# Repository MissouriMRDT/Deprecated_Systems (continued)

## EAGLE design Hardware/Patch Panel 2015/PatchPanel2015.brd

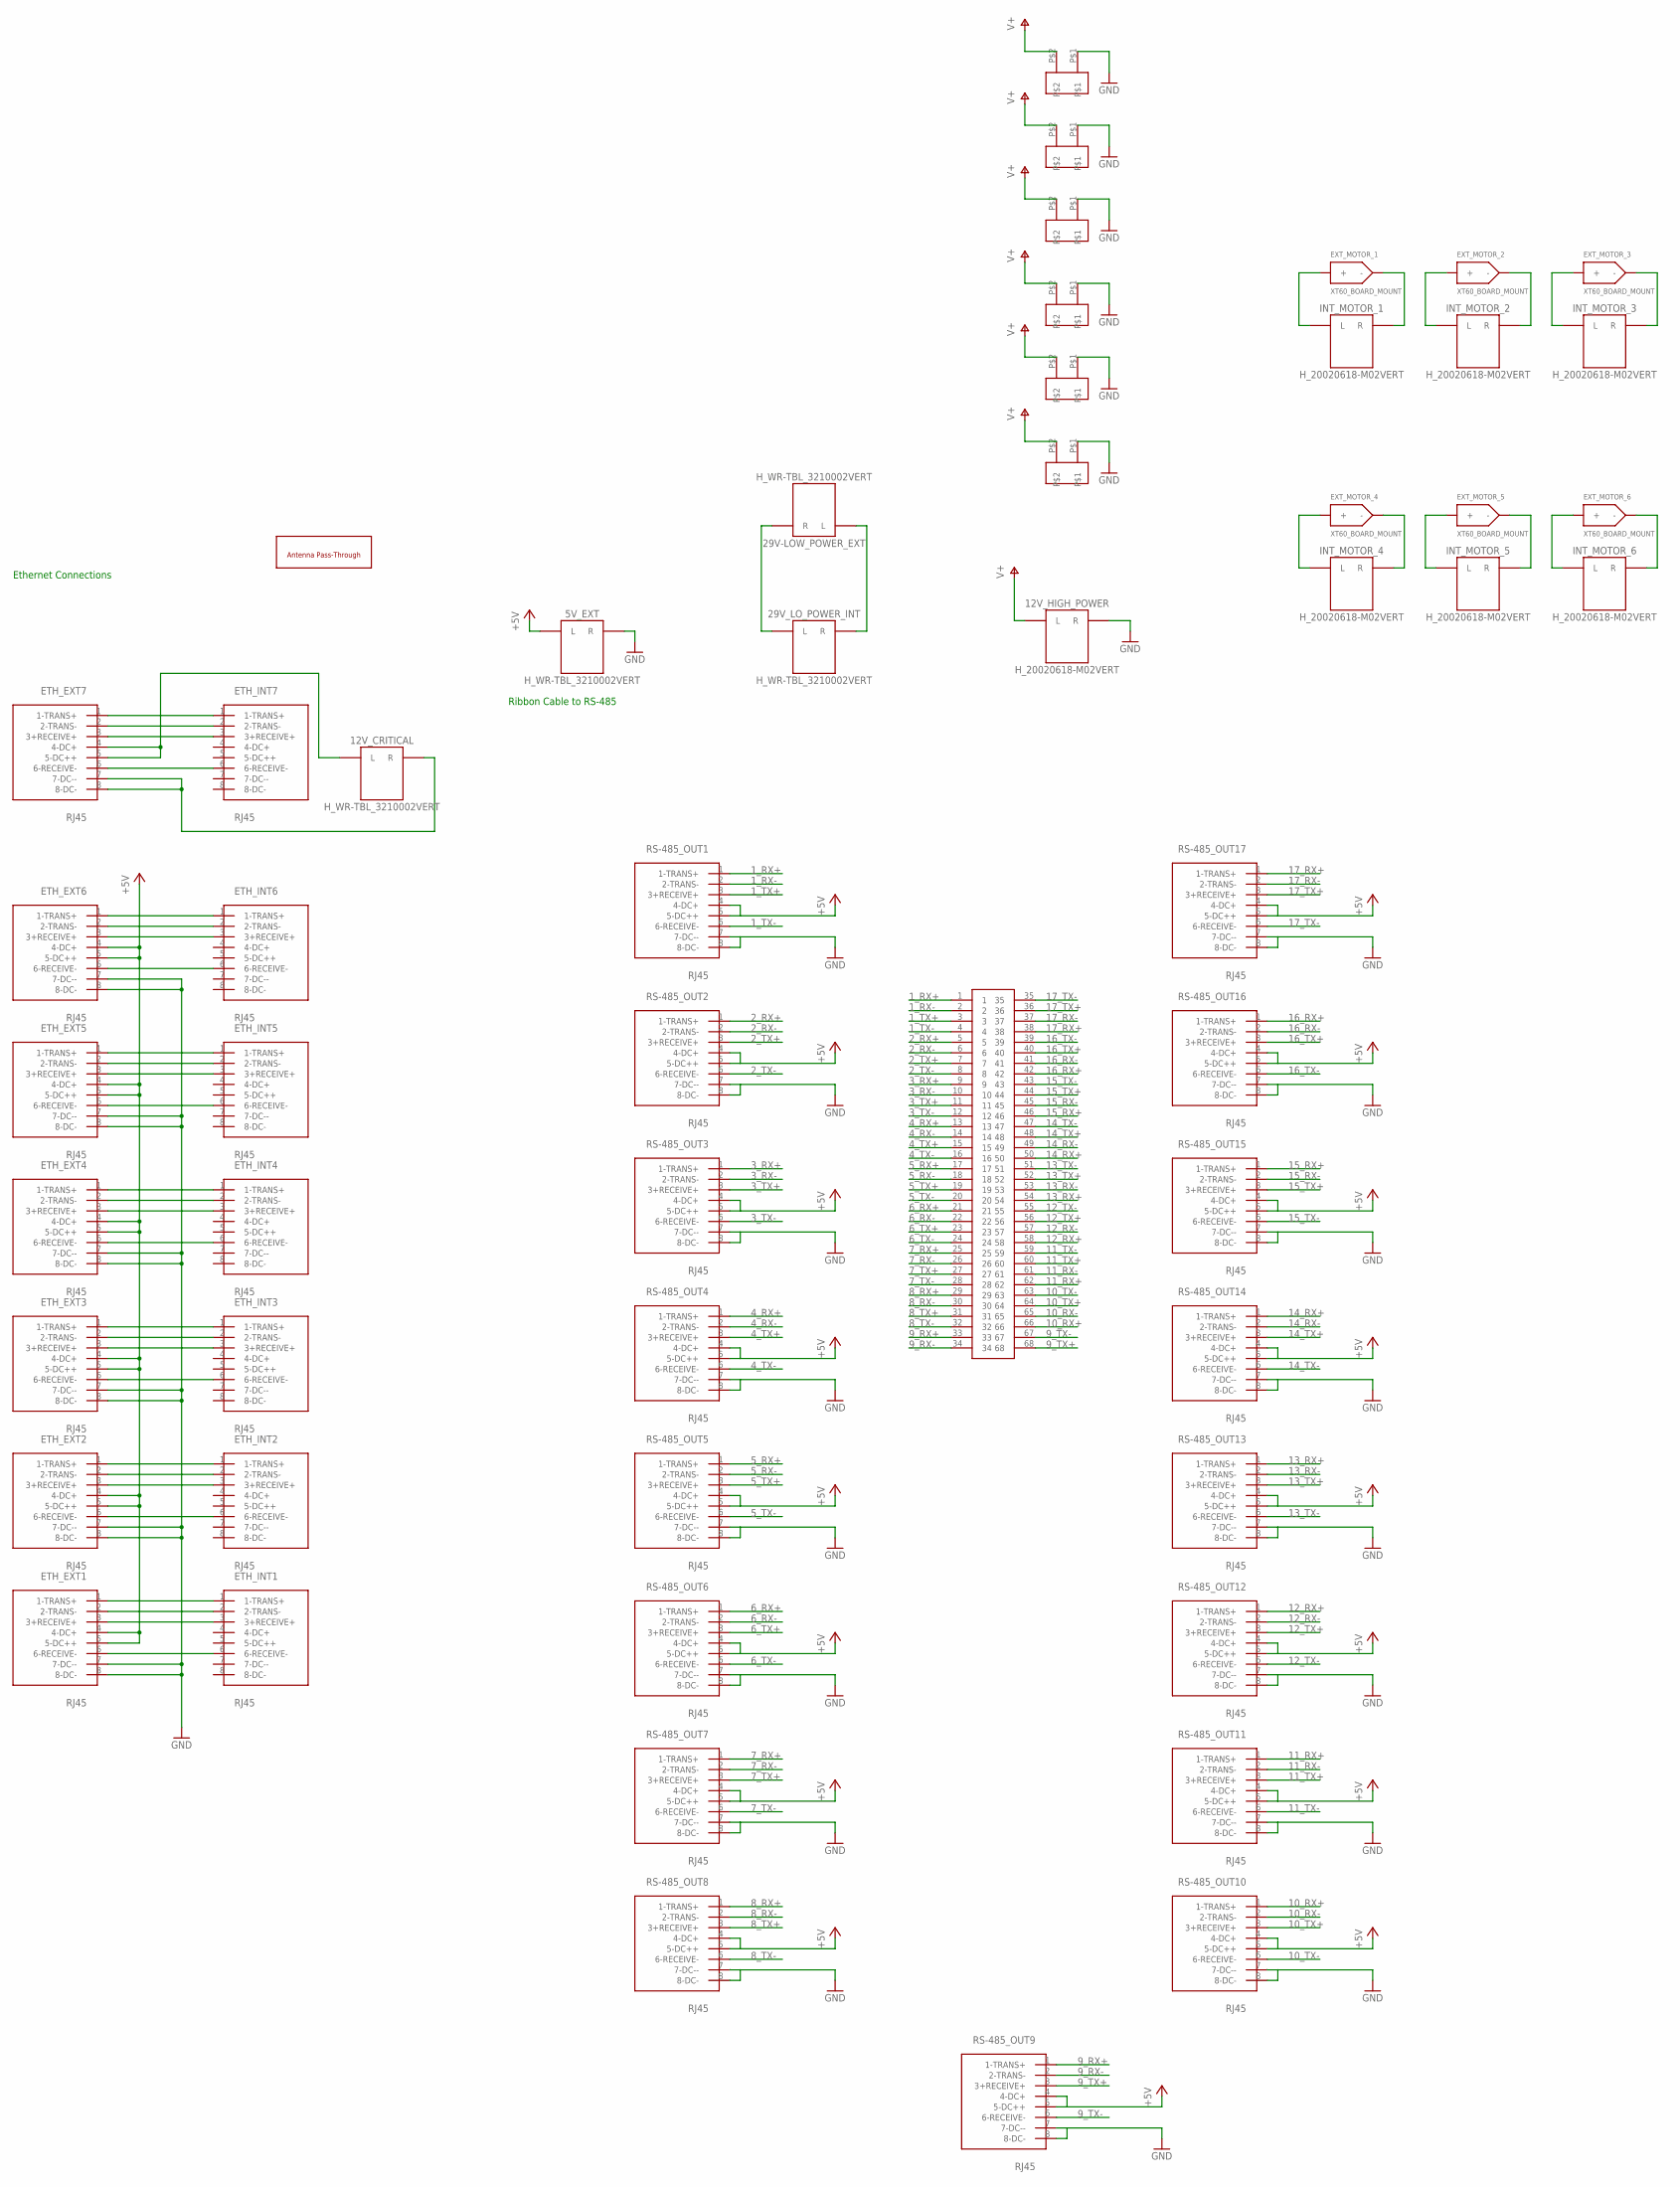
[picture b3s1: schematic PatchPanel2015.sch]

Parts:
5V_EXT, 12V_CRITICAL, 29V-LOW_POWER_EXT, 29V_LO_POWER_INT: H_WR-TBL_3210002VERT; 691321100002
12V_HIGH_POWER: H_20020618-M02VERT; 20020620-M02
ETH_EXT1, ETH_EXT2, ETH_EXT3, ETH_EXT4, ETH_EXT5, ETH_EXT6, ETH_EXT7: RJ45; RJ45-CAT5E
ETH_INT1, ETH_INT2, ETH_INT3, ETH_INT4, ETH_INT5, ETH_INT6, ETH_INT7: RJ45; RJ45-CAT5E
EXT_MOTOR_1, EXT_MOTOR_2, EXT_MOTOR_3, EXT_MOTOR_4, EXT_MOTOR_5, EXT_MOTOR_6: XT60_BOARD_MOUNT; XT60_BOARD
INT_MOTOR_1, INT_MOTOR_2, INT_MOTOR_3, INT_MOTOR_4, INT_MOTOR_5, INT_MOTOR_6: H_20020618-M02VERT; 20020620-M02
RS-485_OUT1, RS-485_OUT2, RS-485_OUT3, RS-485_OUT4, RS-485_OUT5, RS-485_OUT6, RS-485_OUT7, RS-485_OUT8, RS-485_OUT9, RS-485_OUT10, RS-485_OUT11, RS-485_OUT12, RS-485_OUT13, RS-485_OUT14, RS-485_OUT15, RS-485_OUT16, RS-485_OUT17: RJ45; RJ45-CAT5E
U$1, U$2, U$3, U$5, U$6, U$8: MLX-2; 42002-2
U$4: TB60050685100; 60050685100
U$16: SMA-THRU; SMA

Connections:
1_RX+: RS-485_OUT1.1 (1-TRANS+), U$4.1
1_RX-: RS-485_OUT1.2 (2-TRANS-), U$4.2
1_TX+: RS-485_OUT1.3 (3+RECEIVE+), U$4.3
1_TX-: RS-485_OUT1.6 (6-RECEIVE-), U$4.4
2_RX+: RS-485_OUT2.1 (1-TRANS+), U$4.5
2_RX-: RS-485_OUT2.2 (2-TRANS-), U$4.6
2_TX+: RS-485_OUT2.3 (3+RECEIVE+), U$4.7
2_TX-: RS-485_OUT2.6 (6-RECEIVE-), U$4.8
3_RX+: RS-485_OUT3.1 (1-TRANS+), U$4.9
3_RX-: RS-485_OUT3.2 (2-TRANS-), U$4.10
3_TX+: RS-485_OUT3.3 (3+RECEIVE+), U$4.11
3_TX-: RS-485_OUT3.6 (6-RECEIVE-), U$4.12
4_RX+: RS-485_OUT4.1 (1-TRANS+), U$4.13
4_RX-: RS-485_OUT4.2 (2-TRANS-), U$4.14
4_TX+: RS-485_OUT4.3 (3+RECEIVE+), U$4.15
4_TX-: RS-485_OUT4.6 (6-RECEIVE-), U$4.16
5_RX+: RS-485_OUT5.1 (1-TRANS+), U$4.17
5_RX-: RS-485_OUT5.2 (2-TRANS-), U$4.18
5_TX+: RS-485_OUT5.3 (3+RECEIVE+), U$4.19
5_TX-: RS-485_OUT5.6 (6-RECEIVE-), U$4.20
6_RX+: RS-485_OUT6.1 (1-TRANS+), U$4.21
6_RX-: RS-485_OUT6.2 (2-TRANS-), U$4.22
6_TX+: RS-485_OUT6.3 (3+RECEIVE+), U$4.23
6_TX-: RS-485_OUT6.6 (6-RECEIVE-), U$4.24
7_RX+: RS-485_OUT7.1 (1-TRANS+), U$4.25
7_RX-: RS-485_OUT7.2 (2-TRANS-), U$4.26
7_TX+: RS-485_OUT7.3 (3+RECEIVE+), U$4.27
7_TX-: RS-485_OUT7.6 (6-RECEIVE-), U$4.28
8_RX+: RS-485_OUT8.1 (1-TRANS+), U$4.29
8_RX-: RS-485_OUT8.2 (2-TRANS-), U$4.30
8_TX+: RS-485_OUT8.3 (3+RECEIVE+), U$4.31
8_TX-: RS-485_OUT8.6 (6-RECEIVE-), U$4.32
9_RX+: RS-485_OUT9.1 (1-TRANS+), U$4.33
9_RX-: RS-485_OUT9.2 (2-TRANS-), U$4.34
9_TX+: RS-485_OUT9.3 (3+RECEIVE+), U$4.68
9_TX-: RS-485_OUT9.6 (6-RECEIVE-), U$4.67
10_RX+: RS-485_OUT10.1 (1-TRANS+), U$4.66
10_RX-: RS-485_OUT10.2 (2-TRANS-), U$4.65
10_TX+: RS-485_OUT10.3 (3+RECEIVE+), U$4.64
10_TX-: RS-485_OUT10.6 (6-RECEIVE-), U$4.63
11_RX+: RS-485_OUT11.1 (1-TRANS+), U$4.62
11_RX-: RS-485_OUT11.2 (2-TRANS-), U$4.61
11_TX+: RS-485_OUT11.3 (3+RECEIVE+), U$4.60
11_TX-: RS-485_OUT11.6 (6-RECEIVE-), U$4.59
12_RX+: RS-485_OUT12.1 (1-TRANS+), U$4.58
12_RX-: RS-485_OUT12.2 (2-TRANS-), U$4.57
12_TX+: RS-485_OUT12.3 (3+RECEIVE+), U$4.56
12_TX-: RS-485_OUT12.6 (6-RECEIVE-), U$4.55
13_RX+: RS-485_OUT13.1 (1-TRANS+), U$4.54
13_RX-: RS-485_OUT13.2 (2-TRANS-), U$4.53
13_TX+: RS-485_OUT13.3 (3+RECEIVE+), U$4.52
13_TX-: RS-485_OUT13.6 (6-RECEIVE-), U$4.51
14_RX+: RS-485_OUT14.1 (1-TRANS+), U$4.50
14_RX-: RS-485_OUT14.2 (2-TRANS-), U$4.49
14_TX+: RS-485_OUT14.3 (3+RECEIVE+), U$4.48
14_TX-: RS-485_OUT14.6 (6-RECEIVE-), U$4.47
15_RX+: RS-485_OUT15.1 (1-TRANS+), U$4.46
15_RX-: RS-485_OUT15.2 (2-TRANS-), U$4.45
15_TX+: RS-485_OUT15.3 (3+RECEIVE+), U$4.44
15_TX-: RS-485_OUT15.6 (6-RECEIVE-), U$4.43
16_RX+: RS-485_OUT16.1 (1-TRANS+), U$4.42
16_RX-: RS-485_OUT16.2 (2-TRANS-), U$4.41
16_TX+: RS-485_OUT16.3 (3+RECEIVE+), U$4.40
16_TX-: RS-485_OUT16.6 (6-RECEIVE-), U$4.39
17_RX+: RS-485_OUT17.1 (1-TRANS+), U$4.38
17_RX-: RS-485_OUT17.2 (2-TRANS-), U$4.37
17_TX+: RS-485_OUT17.3 (3+RECEIVE+), U$4.36
17_TX-: RS-485_OUT17.6 (6-RECEIVE-), U$4.35
+5V: 5V_EXT.L, ETH_EXT1.4 (4-DC+), ETH_EXT1.5 (5-DC++), ETH_EXT2.4 (4-DC+), ETH_EXT2.5 (5-DC++), ETH_EXT3.4 (4-DC+), ETH_EXT3.5 (5-DC++), ETH_EXT4.4 (4-DC+), ETH_EXT4.5 (5-DC++), ETH_EXT5.4 (4-DC+), ETH_EXT5.5 (5-DC++), ETH_EXT6.4 (4-DC+), ETH_EXT6.5 (5-DC++), RS-485_OUT1.4 (4-DC+), RS-485_OUT1.5 (5-DC++), RS-485_OUT2.4 (4-DC+), RS-485_OUT2.5 (5-DC++), RS-485_OUT3.4 (4-DC+), RS-485_OUT3.5 (5-DC++), RS-485_OUT4.4 (4-DC+), RS-485_OUT4.5 (5-DC++), RS-485_OUT5.4 (4-DC+), RS-485_OUT5.5 (5-DC++), RS-485_OUT6.4 (4-DC+), RS-485_OUT6.5 (5-DC++), RS-485_OUT7.4 (4-DC+), RS-485_OUT7.5 (5-DC++), RS-485_OUT8.4 (4-DC+), RS-485_OUT8.5 (5-DC++), RS-485_OUT9.4 (4-DC+), RS-485_OUT9.5 (5-DC++), RS-485_OUT10.4 (4-DC+), RS-485_OUT10.5 (5-DC++), RS-485_OUT11.4 (4-DC+), RS-485_OUT11.5 (5-DC++), RS-485_OUT12.4 (4-DC+), RS-485_OUT12.5 (5-DC++), RS-485_OUT13.4 (4-DC+), RS-485_OUT13.5 (5-DC++), RS-485_OUT14.4 (4-DC+), RS-485_OUT14.5 (5-DC++), RS-485_OUT15.4 (4-DC+), RS-485_OUT15.5 (5-DC++), RS-485_OUT16.4 (4-DC+), RS-485_OUT16.5 (5-DC++), RS-485_OUT17.4 (4-DC+), RS-485_OUT17.5 (5-DC++)
GND: 5V_EXT.R, 12V_HIGH_POWER.R1 (R), 12V_HIGH_POWER.R2 (R), ETH_EXT1.7 (7-DC--), ETH_EXT1.8 (8-DC-), ETH_EXT2.7 (7-DC--), ETH_EXT2.8 (8-DC-), ETH_EXT3.7 (7-DC--), ETH_EXT3.8 (8-DC-), ETH_EXT4.7 (7-DC--), ETH_EXT4.8 (8-DC-), ETH_EXT5.7 (7-DC--), ETH_EXT5.8 (8-DC-), ETH_EXT6.7 (7-DC--), ETH_EXT6.8 (8-DC-), RS-485_OUT1.7 (7-DC--), RS-485_OUT1.8 (8-DC-), RS-485_OUT2.7 (7-DC--), RS-485_OUT2.8 (8-DC-), RS-485_OUT3.7 (7-DC--), RS-485_OUT3.8 (8-DC-), RS-485_OUT4.7 (7-DC--), RS-485_OUT4.8 (8-DC-), RS-485_OUT5.7 (7-DC--), RS-485_OUT5.8 (8-DC-), RS-485_OUT6.7 (7-DC--), RS-485_OUT6.8 (8-DC-), RS-485_OUT7.7 (7-DC--), RS-485_OUT7.8 (8-DC-), RS-485_OUT8.7 (7-DC--), RS-485_OUT8.8 (8-DC-), RS-485_OUT9.7 (7-DC--), RS-485_OUT9.8 (8-DC-), RS-485_OUT10.7 (7-DC--), RS-485_OUT10.8 (8-DC-), RS-485_OUT11.7 (7-DC--), RS-485_OUT11.8 (8-DC-), RS-485_OUT12.7 (7-DC--), RS-485_OUT12.8 (8-DC-), RS-485_OUT13.7 (7-DC--), RS-485_OUT13.8 (8-DC-), RS-485_OUT14.7 (7-DC--), RS-485_OUT14.8 (8-DC-), RS-485_OUT15.7 (7-DC--), RS-485_OUT15.8 (8-DC-), RS-485_OUT16.7 (7-DC--), RS-485_OUT16.8 (8-DC-), RS-485_OUT17.7 (7-DC--), RS-485_OUT17.8 (8-DC-), U$1.P$1, U$2.P$1, U$3.P$1, U$5.P$1, U$6.P$1, U$8.P$1
unnamed: ETH_EXT1.1 (1-TRANS+), ETH_INT1.1 (1-TRANS+)
unnamed: ETH_EXT1.2 (2-TRANS-), ETH_INT1.2 (2-TRANS-)
unnamed: ETH_EXT1.3 (3+RECEIVE+), ETH_INT1.3 (3+RECEIVE+)
unnamed: EXT_MOTOR_1.POS (+), INT_MOTOR_1.L1 (L), INT_MOTOR_1.L2 (L)
unnamed: EXT_MOTOR_1.NEG (-), INT_MOTOR_1.R1 (R), INT_MOTOR_1.R2 (R)
unnamed: ETH_EXT1.6 (6-RECEIVE-), ETH_INT1.6 (6-RECEIVE-)
unnamed: EXT_MOTOR_2.POS (+), INT_MOTOR_2.L1 (L), INT_MOTOR_2.L2 (L)
unnamed: EXT_MOTOR_2.NEG (-), INT_MOTOR_2.R1 (R), INT_MOTOR_2.R2 (R)
unnamed: ETH_EXT2.1 (1-TRANS+), ETH_INT2.1 (1-TRANS+)
unnamed: ETH_EXT2.2 (2-TRANS-), ETH_INT2.2 (2-TRANS-)
unnamed: ETH_EXT2.3 (3+RECEIVE+), ETH_INT2.3 (3+RECEIVE+)
unnamed: EXT_MOTOR_3.POS (+), INT_MOTOR_3.L1 (L), INT_MOTOR_3.L2 (L)
unnamed: EXT_MOTOR_3.NEG (-), INT_MOTOR_3.R1 (R), INT_MOTOR_3.R2 (R)
unnamed: ETH_EXT2.6 (6-RECEIVE-), ETH_INT2.6 (6-RECEIVE-)
unnamed: EXT_MOTOR_4.POS (+), INT_MOTOR_4.L1 (L), INT_MOTOR_4.L2 (L)
unnamed: EXT_MOTOR_4.NEG (-), INT_MOTOR_4.R1 (R), INT_MOTOR_4.R2 (R)
unnamed: ETH_EXT3.1 (1-TRANS+), ETH_INT3.1 (1-TRANS+)
unnamed: ETH_EXT3.2 (2-TRANS-), ETH_INT3.2 (2-TRANS-)
unnamed: ETH_EXT3.3 (3+RECEIVE+), ETH_INT3.3 (3+RECEIVE+)
unnamed: EXT_MOTOR_5.POS (+), INT_MOTOR_5.L1 (L), INT_MOTOR_5.L2 (L)
unnamed: EXT_MOTOR_5.NEG (-), INT_MOTOR_5.R1 (R), INT_MOTOR_5.R2 (R)
unnamed: ETH_EXT3.6 (6-RECEIVE-), ETH_INT3.6 (6-RECEIVE-)
unnamed: EXT_MOTOR_6.POS (+), INT_MOTOR_6.L1 (L), INT_MOTOR_6.L2 (L)
unnamed: EXT_MOTOR_6.NEG (-), INT_MOTOR_6.R1 (R), INT_MOTOR_6.R2 (R)
unnamed: 29V-LOW_POWER_EXT.R, 29V_LO_POWER_INT.L
unnamed: ETH_EXT4.6 (6-RECEIVE-), ETH_INT4.6 (6-RECEIVE-)
unnamed: 29V-LOW_POWER_EXT.L, 29V_LO_POWER_INT.R
unnamed: 12V_CRITICAL.L, ETH_EXT7.4 (4-DC+), ETH_EXT7.5 (5-DC++)
unnamed: ETH_EXT4.3 (3+RECEIVE+), ETH_INT4.3 (3+RECEIVE+)
unnamed: ETH_EXT4.2 (2-TRANS-), ETH_INT4.2 (2-TRANS-)
unnamed: ETH_EXT4.1 (1-TRANS+), ETH_INT4.1 (1-TRANS+)
unnamed: 12V_CRITICAL.R, ETH_EXT7.7 (7-DC--), ETH_EXT7.8 (8-DC-)
unnamed: ETH_EXT5.6 (6-RECEIVE-), ETH_INT5.6 (6-RECEIVE-)
unnamed: ETH_EXT5.3 (3+RECEIVE+), ETH_INT5.3 (3+RECEIVE+)
unnamed: ETH_EXT5.2 (2-TRANS-), ETH_INT5.2 (2-TRANS-)
unnamed: ETH_EXT5.1 (1-TRANS+), ETH_INT5.1 (1-TRANS+)
unnamed: ETH_EXT6.1 (1-TRANS+), ETH_INT6.1 (1-TRANS+)
unnamed: ETH_EXT6.2 (2-TRANS-), ETH_INT6.2 (2-TRANS-)
unnamed: ETH_EXT6.3 (3+RECEIVE+), ETH_INT6.3 (3+RECEIVE+)
unnamed: ETH_EXT6.6 (6-RECEIVE-), ETH_INT6.6 (6-RECEIVE-)
unnamed: ETH_EXT7.1 (1-TRANS+), ETH_INT7.1 (1-TRANS+)
unnamed: ETH_EXT7.2 (2-TRANS-), ETH_INT7.2 (2-TRANS-)
unnamed: ETH_EXT7.3 (3+RECEIVE+), ETH_INT7.3 (3+RECEIVE+)
unnamed: ETH_EXT7.6 (6-RECEIVE-), ETH_INT7.6 (6-RECEIVE-)
V+: 12V_HIGH_POWER.L1 (L), 12V_HIGH_POWER.L2 (L), U$1.P$2, U$2.P$2, U$3.P$2, U$5.P$2, U$6.P$2, U$8.P$2

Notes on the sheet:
Ethernet Connections
Ribbon Cable to RS-485

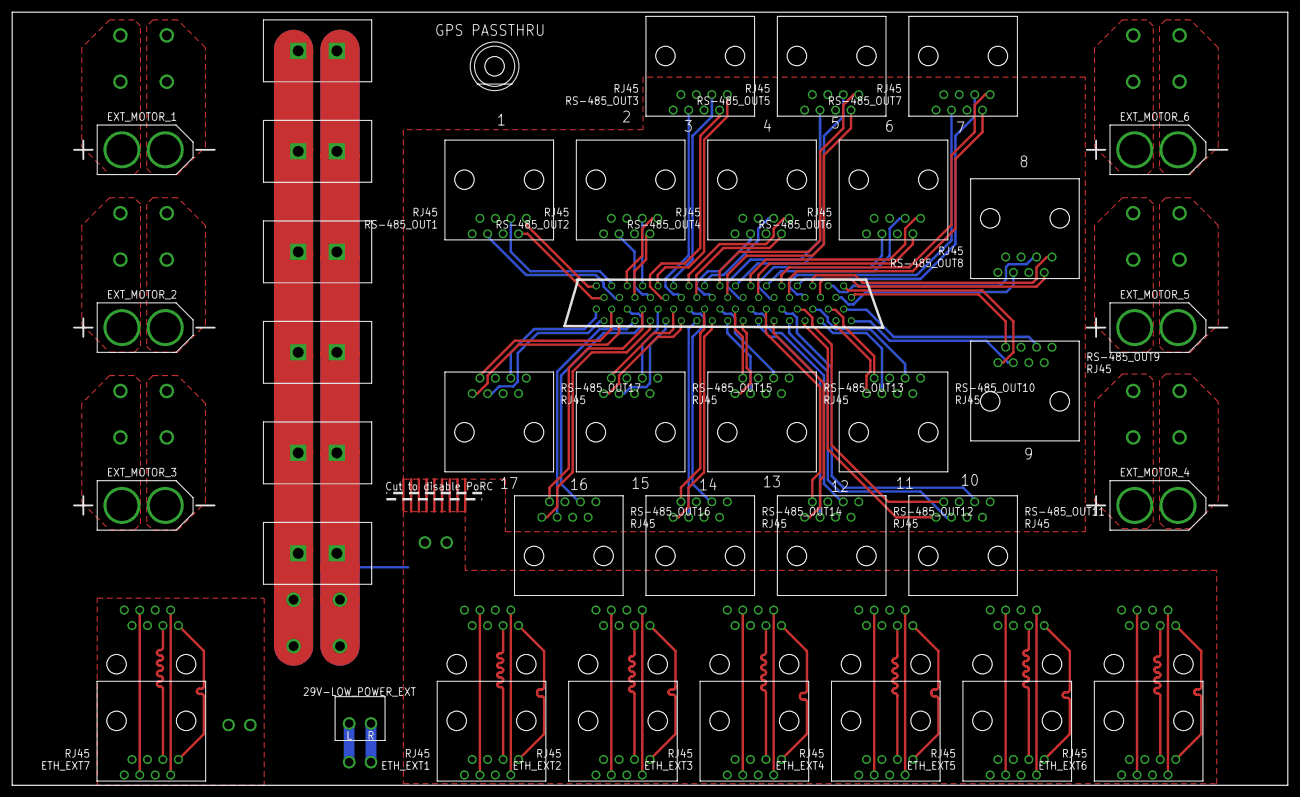
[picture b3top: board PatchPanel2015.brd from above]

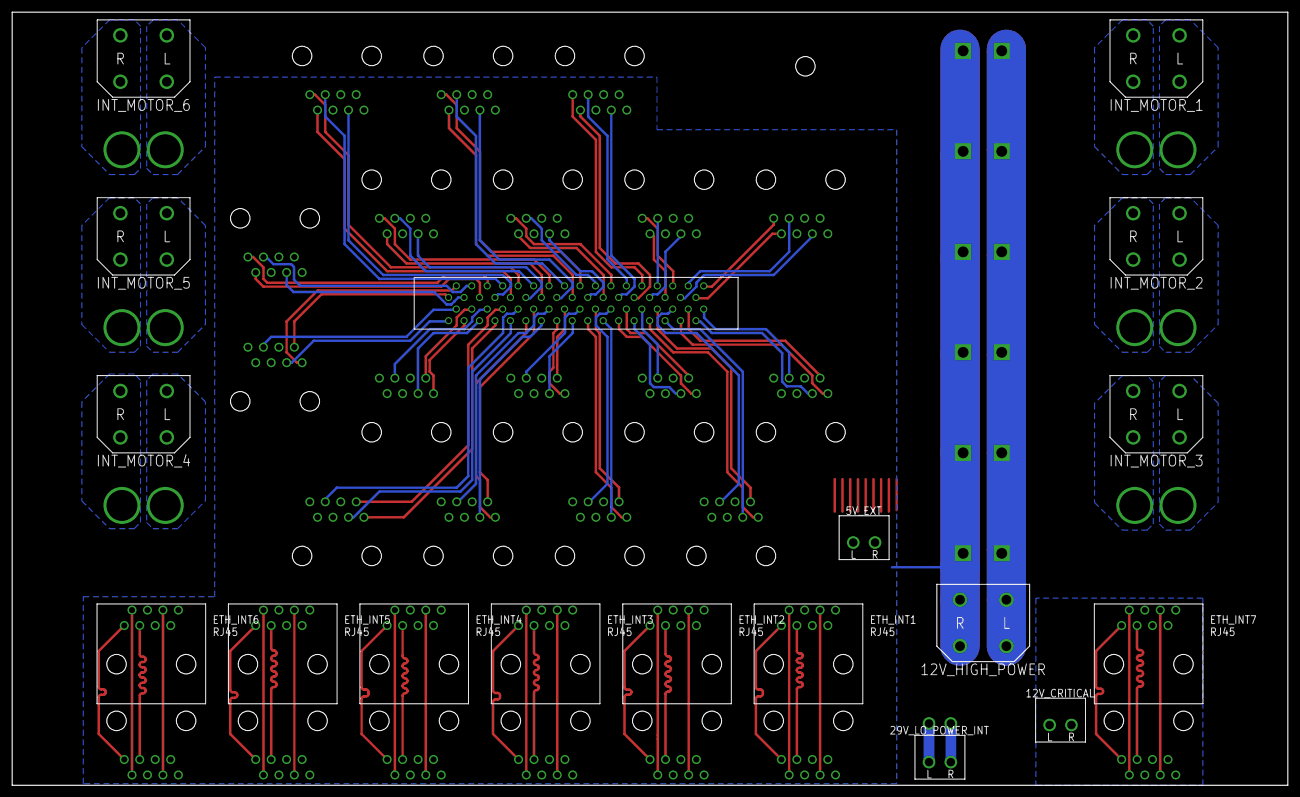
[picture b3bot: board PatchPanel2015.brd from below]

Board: 2 copper layers, 209.6 x 127.0 mm, 56 parts (18 on the bottom side), 115 nets.

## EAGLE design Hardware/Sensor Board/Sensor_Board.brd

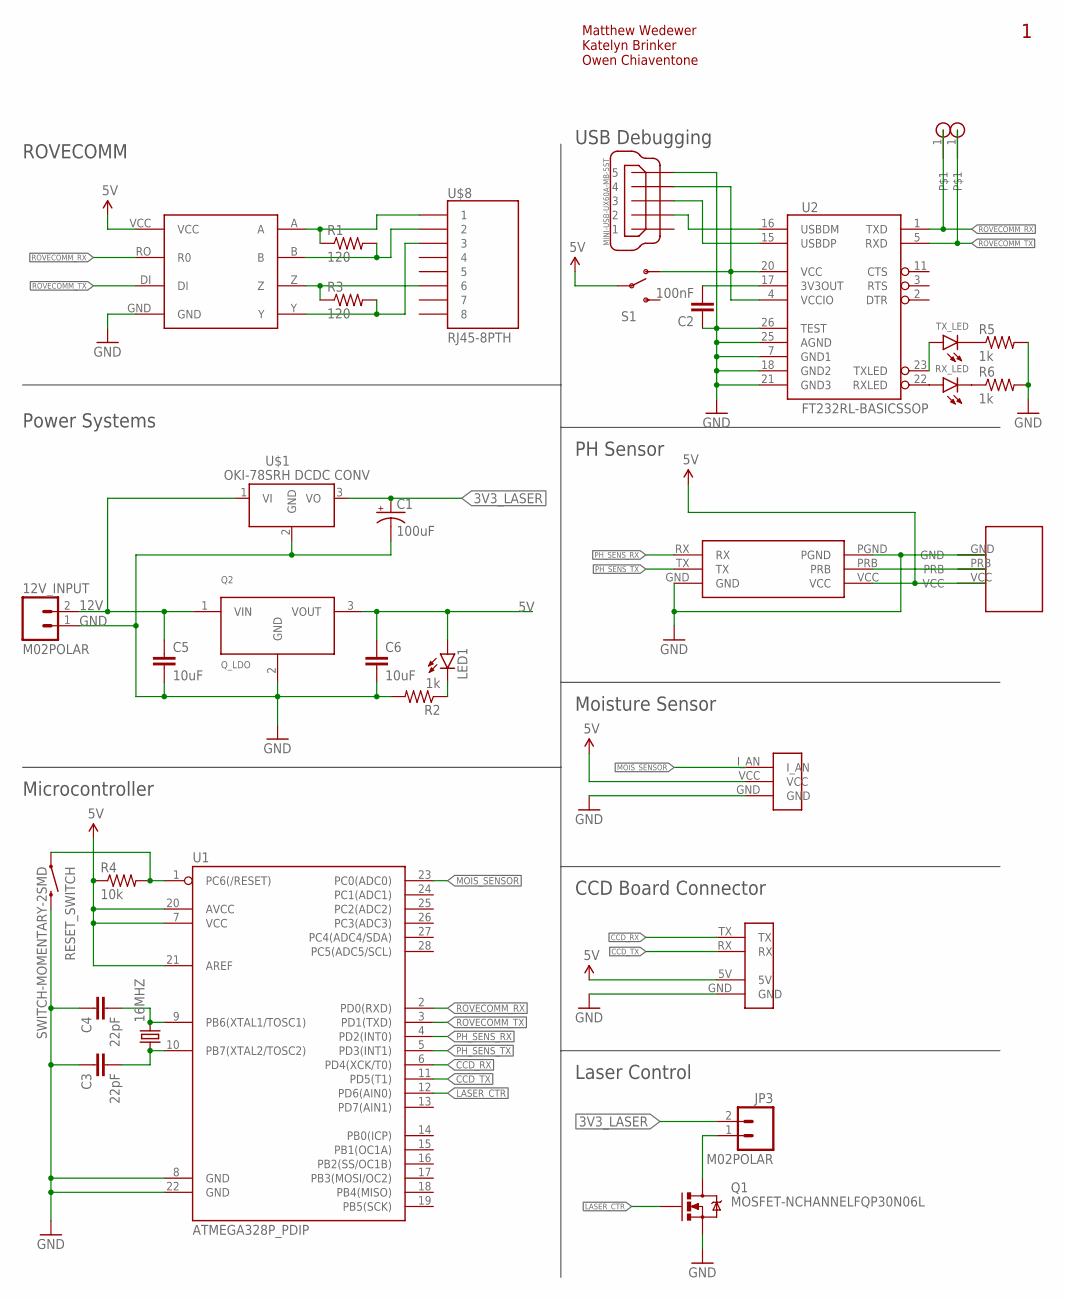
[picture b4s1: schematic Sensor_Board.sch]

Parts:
12V_INPUT: M02POLAR; MOLEX-1X2
16MHZ: CRYSTALHC49US; HC49US
C1: 100uF; CPOL-RADIAL-100UF-25V
C2: 100nF; 1206
C3, C4: 22pF; 1206
C5, C6: 10uF; 1206
DEBUG_RX: J_HOLE; J_AWG20
DEBUG_TX: J_HOLE; J_AWG20
JP3: M02POLAR; MOLEX-1X2
LED1: LED1206; LED-1206
Q1: MOSFET-NCHANNELFQP30N06L; TO220V
Q2: Q_LDO; TO-220
R1, R3: 120; 1206
R2, R5, R6: 1k; 1206
R4: 10k; 1206
RESET_SWITCH: SWITCH-MOMENTARY-2SMD; TACTILE-SWITCH-SMD
RX_LED: LED1206; LED-1206
S1: SWITCH-SPDTPTH; SWITCH-SPDT
TX_LED: LED1206; LED-1206
U1: ATMEGA328P_PDIP; DIL28-3
U2: FT232RL-BASICSSOP; SSOP28DB
U$1: Q_OKI-78SR; OKI-78SRH
U$3: PH_EZ0
U$4: PH_CONNECTOR
U$5: MOISTURE_SENSOR
U$6: CCD_CONNECTOR
U$7: MAX3077; MAX3070E
U$8: RJ45-8PTH; RJ45-8
X1: MINI-USB-UX60A-MB-5ST; UX60A-MB-5ST

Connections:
3V3_LASER: C1.1 (+), JP3.2, U$1.3 (VO)
5V: C6.1, LED1.A, Q2.3 (VOUT), R4.1, S1.2, U1.7 (VCC), U1.20 (AVCC), U1.21 (AREF), U$3.VCC, U$4.VCC, U$5.VCC, U$6.5V, U$7.VCC
5V1: TX_LED.A, U2.23 (TXLED)
12V: 12V_INPUT.2, C5.1, Q2.1 (VIN), U$1.1 (VI)
CCD_RX: U1.6 (PD4(XCK/T0)), U$6.TX
CCD_TX: U1.11 (PD5(T1)), U$6.RX
GND: 12V_INPUT.1, C1.2 (-), C2.1, C3.1, C4.1, C5.2, C6.2, Q1.3 (S), Q2.2 (GND), R2.2, R5.2, R6.2, RESET_SWITCH.3 (2), U1.8 (GND), U1.22 (GND), U2.7 (GND1), U2.18 (GND2), U2.21 (GND3), U2.25 (AGND), U2.26 (TEST), U$1.2 (GND), U$3.GND, U$3.PGND, U$4.GND, U$5.GND, U$6.GND, U$7.GND, X1.5
LASER_CTR: Q1.1 (G), U1.12 (PD6(AIN0))
MOIS_SENSOR: U1.23 (PC0(ADC0)), U$5.I_AN
unnamed: JP3.1, Q1.2 (D)
unnamed: 16MHZ.2, C4.2, U1.9 (PB6(XTAL1/TOSC1))
unnamed: LED1.C, R2.1
unnamed: 16MHZ.1, C3.2, U1.10 (PB7(XTAL2/TOSC2))
unnamed: U$3.PRB, U$4.PRB
unnamed: R1.1, U$7.A, U$8.1
unnamed: R1.2, U$7.B, U$8.2
unnamed: R3.1, U$7.Z, U$8.6
unnamed: R3.2, U$7.Y, U$8.3
unnamed: R4.2, RESET_SWITCH.1, U1.1 (PC6(/RESET))
unnamed: C2.2, U2.17 (3V3OUT)
unnamed: U2.16 (USBDM), X1.2
unnamed: U2.15 (USBDP), X1.3
unnamed: S1.1 (O), U2.4 (VCCIO), U2.20 (VCC), X1.4
unnamed: R5.1, TX_LED.C
unnamed: RX_LED.A, U2.22 (RXLED)
unnamed: R6.1, RX_LED.C
PH_SENS_RX: U1.4 (PD2(INT0)), U$3.RX
PH_SENS_TX: U1.5 (PD3(INT1)), U$3.TX
ROVECOMM_RX: DEBUG_RX.1, U1.2 (PD0(RXD)), U2.1 (TXD), U$7.RO (R0)
ROVECOMM_TX: DEBUG_TX.1, U1.3 (PD1(TXD)), U2.5 (RXD), U$7.DI

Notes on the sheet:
Laser Control
CCD Board Connector
PH Sensor
Moisture Sensor
Power Systems
Microcontroller
ROVECOMM
USB Debugging
Matthew Wedewer Katelyn Brinker Owen Chiaventone

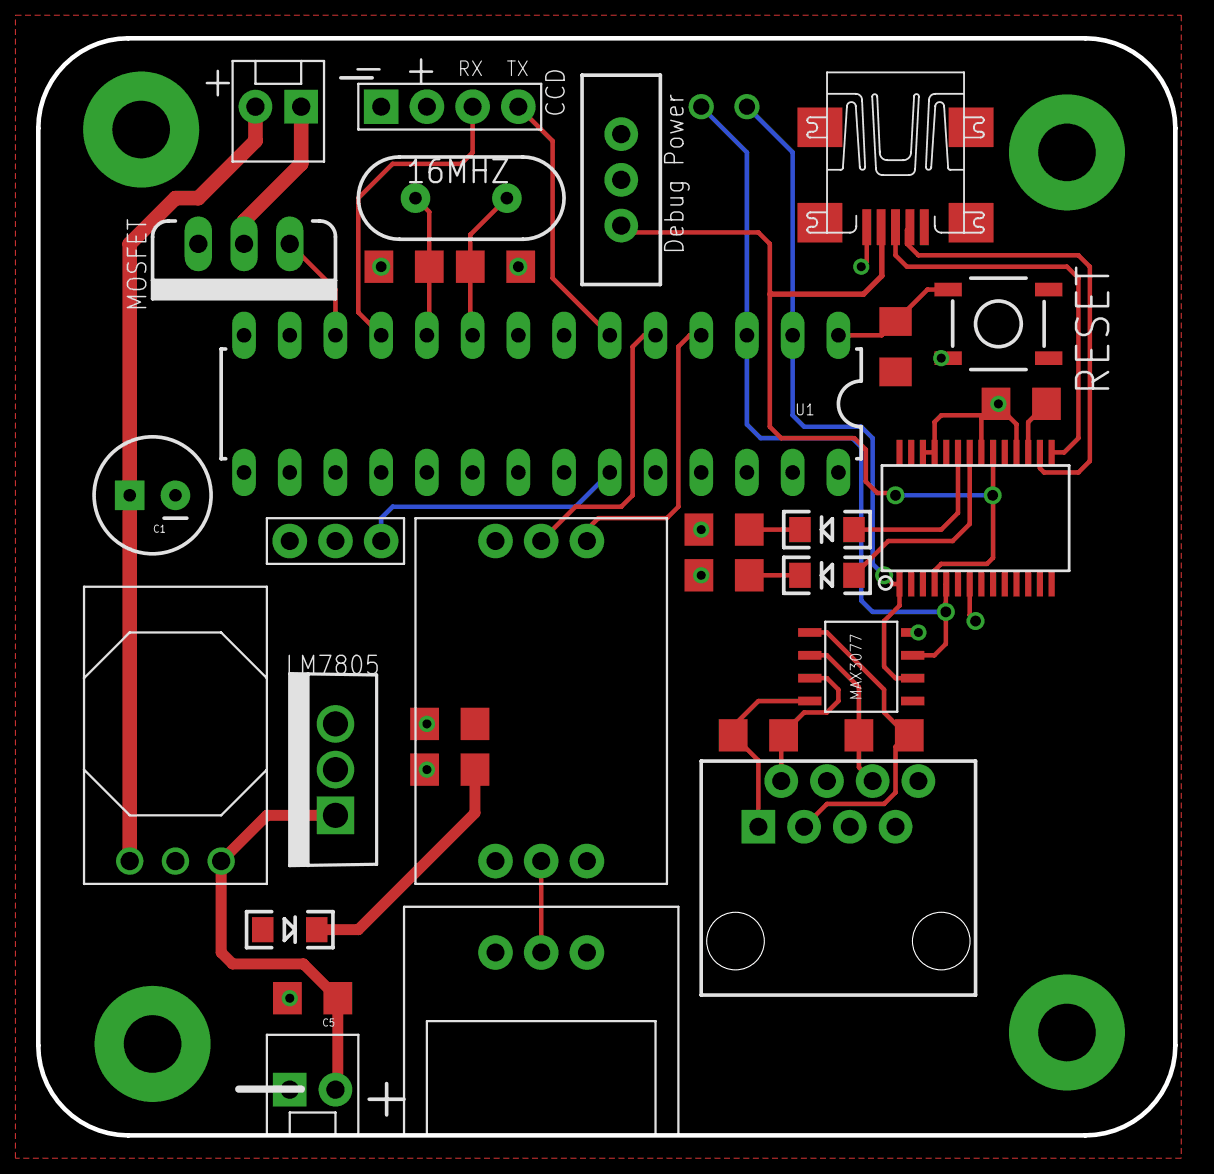
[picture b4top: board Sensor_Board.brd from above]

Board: 2 copper layers, 63.2 x 61.0 mm, 34 parts (0 on the bottom side), 30 nets.

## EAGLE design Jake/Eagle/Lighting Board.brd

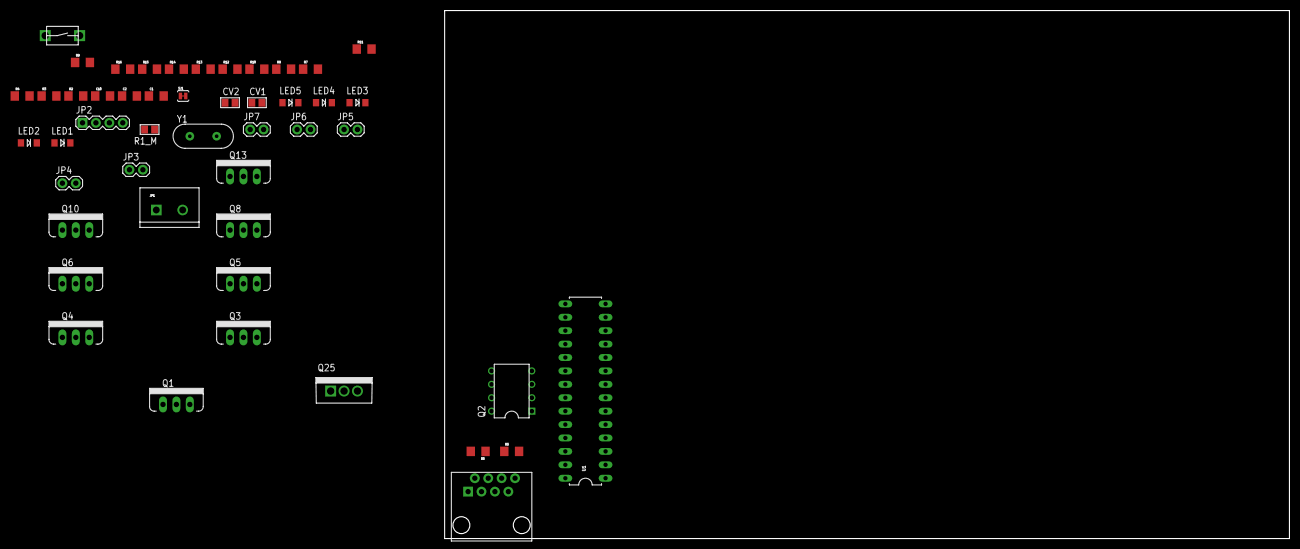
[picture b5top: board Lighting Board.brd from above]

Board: 2 copper layers, 160.0 x 100.0 mm, 48 parts (0 on the bottom side), 34 nets, no tracks yet.

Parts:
C1, C2: 0.1uF; 1206
C10: .1uF; 1206
CV1, CV2: C_0805
JP1: M025MM; SCREWTERMINAL-5MM-2
JP2: 1X04
JP3, JP4, JP5, JP6, JP7: M02PTH; 1X02
LED1, LED2, LED3, LED4, LED5: LED-1206
MS: J_MC32857; J_TOGGLE
Q1, Q3, Q4, Q5, Q6, Q8, Q10, Q13: MOSFET-NCHANNELFQP30N06L; TO220V
Q2: Q_LTC490; DIP8
Q25: LDO; TO-220
R1_M: 200; R_0805
R2, R3, R4, R7, R8, R10, R12, R15: 1k; 1206
R5, R6: 120 Ohm; 1206
R9, R11: 1206
R13, R14, R16: 200; 1206
SJ1: SOLDERJUMPERTRACE; SJ_2S-TRACE
U1: ATMEGA328P_PDIP; DIL28-3
U$1: RJ45-8PTH; RJ45-8
Y1: HC49US

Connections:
D1: Q10.1, R12.2, U1.13
D2: Q13.1, R15.2, U1.14
GND: C1.2, C2.2, C10.2, CV1.2, CV2.2, JP1.2, MS.P$1, Q1.3, Q2.4, Q3.3, Q4.3, Q5.3, Q6.3, Q8.3, Q10.3, Q13.3, Q25.2, R2.1, R3.1, R4.1, R7.1, R8.1, R10.1, R12.1, R15.1, SJ1.1, U1.8, U1.22
unnamed: Q2.5, R6.2, U$1.1
unnamed: C2.1, U1.10, Y1.1
unnamed: LED1.A, R9.1
unnamed: LED2.A, R11.1
unnamed: LED3.A, R13.1
unnamed: LED4.A, R14.1
unnamed: LED5.A, R16.1
unnamed: Q2.6, R6.1, U$1.2
unnamed: Q2.7, R5.2, U$1.6
unnamed: Q2.8, R5.1, U$1.3
unnamed: SJ1.2, U$1.7, U$1.8
unnamed: C1.1, U1.9, Y1.2
unnamed: JP2.2, Q1.2
unnamed: JP2.3, Q3.2
unnamed: JP2.4, Q4.2
unnamed: MS.P$2, R1_M.1, U1.1
N%2: JP4.2, LED3.C, Q6.2
N%3: JP3.2, LED4.C, Q5.2
N%106: JP5.2, LED5.C, Q8.2
N%107: JP6.2, LED2.C, Q10.2
N%110: JP7.2, LED1.C, Q13.2
PWM1: Q3.1, R3.2, U1.5
PWM2: Q4.1, R4.2, U1.11
PWM3: Q1.1, R2.2, U1.12
PWM4: Q5.1, R7.2, U1.15
PWM5: Q6.1, R8.2, U1.16
PWM6: Q8.1, R10.2, U1.17
RXD: Q2.2, U1.2
TXD: Q2.3, U1.3
V5: C10.1, CV2.1, Q2.1, Q25.3, R1_M.2, U1.7, U1.20
VIN: CV1.1, JP1.1, JP2.1, JP3.1, JP4.1, JP5.1, JP6.1, JP7.1, Q25.1, R9.2, R11.2, R13.2, R14.2, R16.2
